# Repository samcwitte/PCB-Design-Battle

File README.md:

# PCB-Design-Battle

This is a repository containing my PCB designs for a 2-hour PCB battle I participated in with [Predictable Designs on YouTube](https://www.youtube.com/@PredictableDesigns).

The video hasn't been released yet, but I'll update this line when it is.

## Summary

This design battle was to take place over the course of 2 hours, during which the participants and I would have to complete the schematic capture and PCB layout. Here's the design guidelines we were given:

> Design a small, battery-powered PCB that reads temperature and sends the data wirelessly to a mobile app. The device must also indicate the temperature locally, this could be a display, an LED (flashing speed or color indicates temp), or something else creative. You can use any MCU, sensor, wireless method, and battery type (rechargeable, coin cells, or alkalines). You have 2 hours to complete the design.

There are two folders in this repository.
- `ESP_32_Battle` is my official end result of the 2 hour battle
- `ESP_32_Battle_4h` is the result of giving myself an additional 2 hours to work on the PCB

I took inspiration from a few of my previous ESP32 designs, of which this board shares many similarities.

While I hope they would work if made, I make no guarantees to the functionality of these PCBs.

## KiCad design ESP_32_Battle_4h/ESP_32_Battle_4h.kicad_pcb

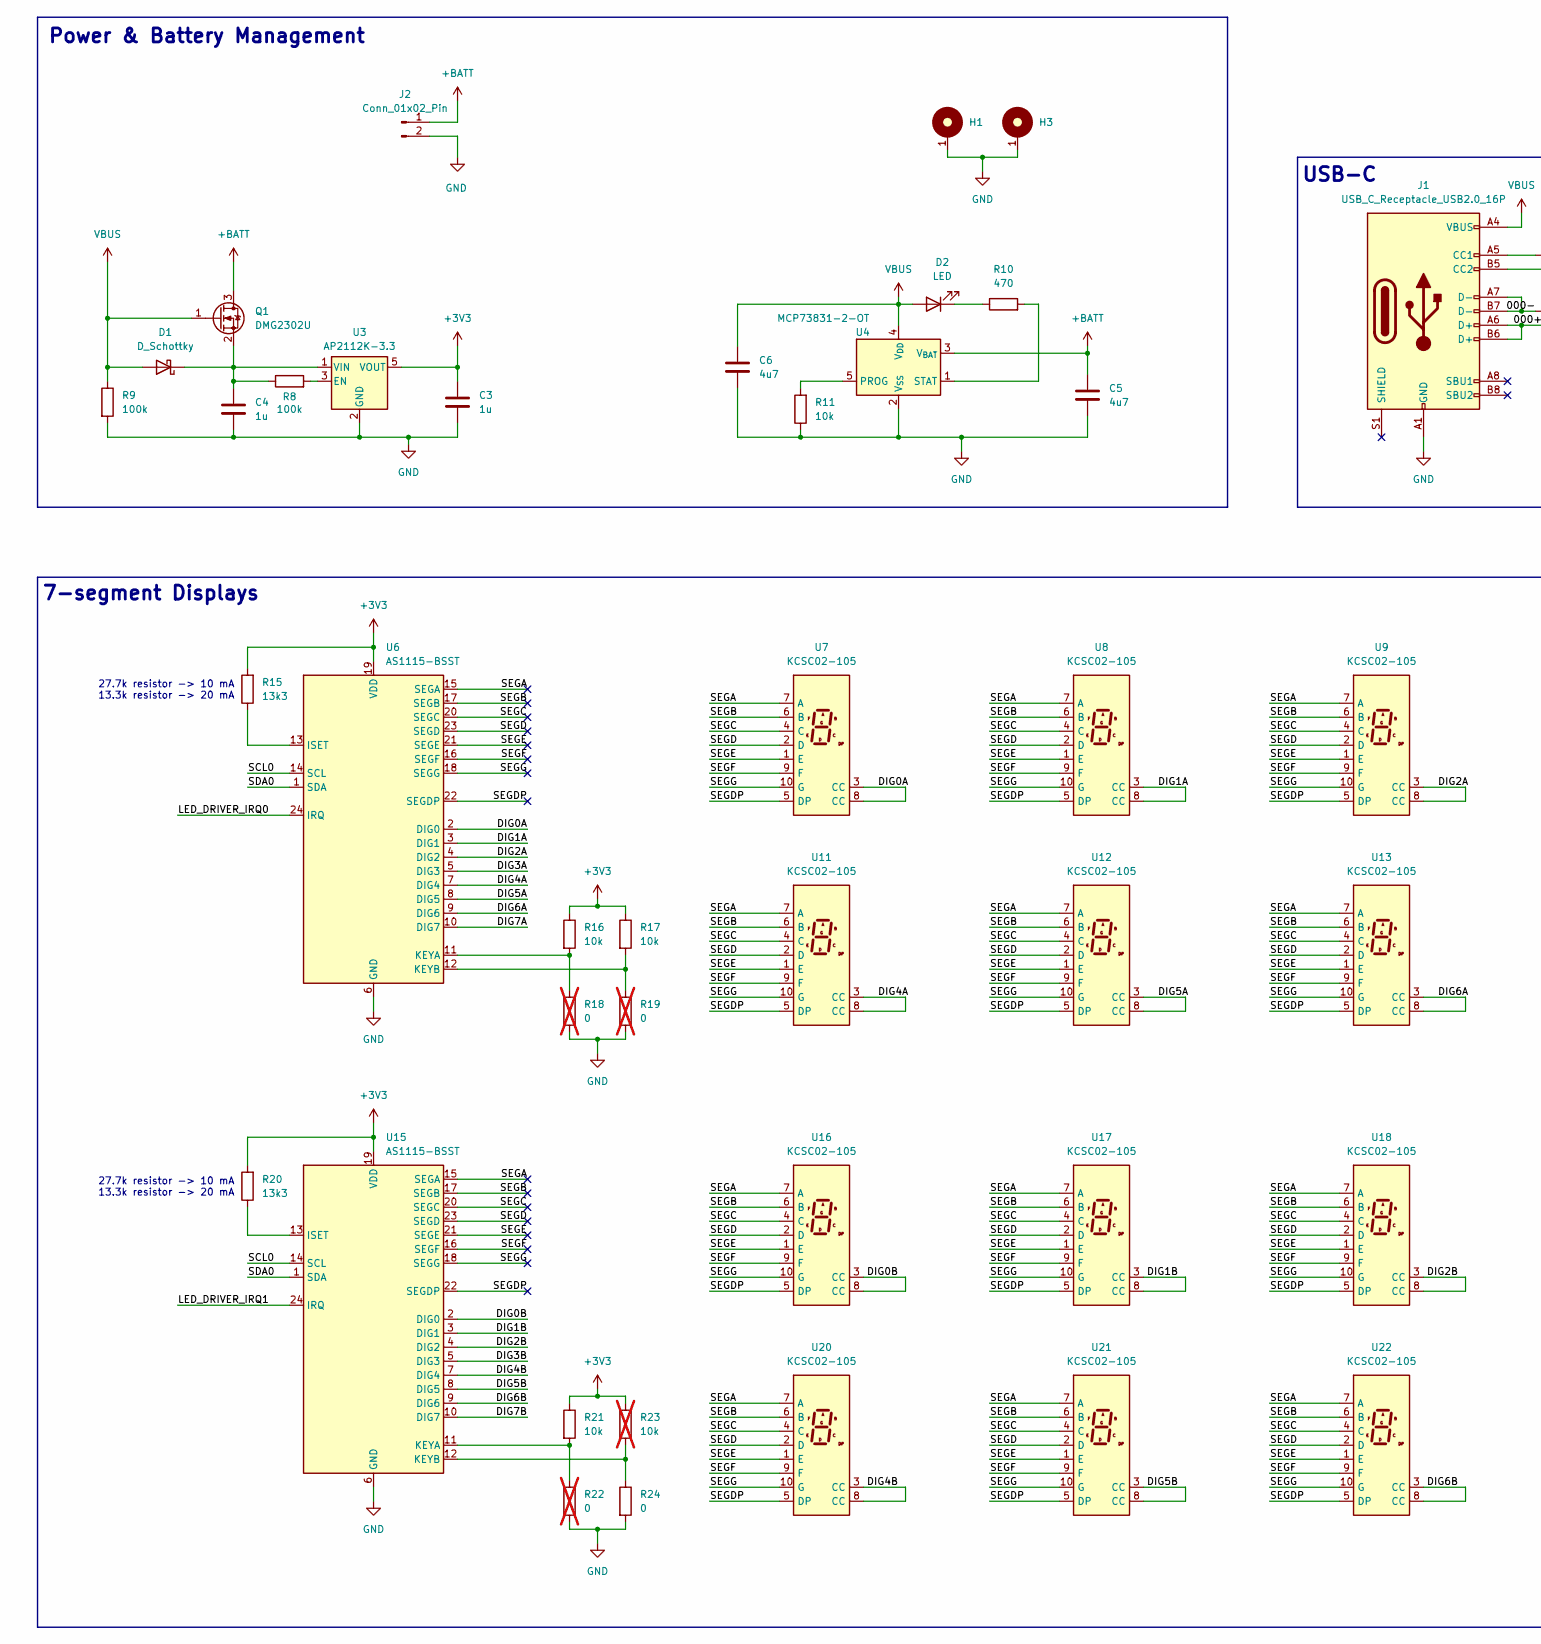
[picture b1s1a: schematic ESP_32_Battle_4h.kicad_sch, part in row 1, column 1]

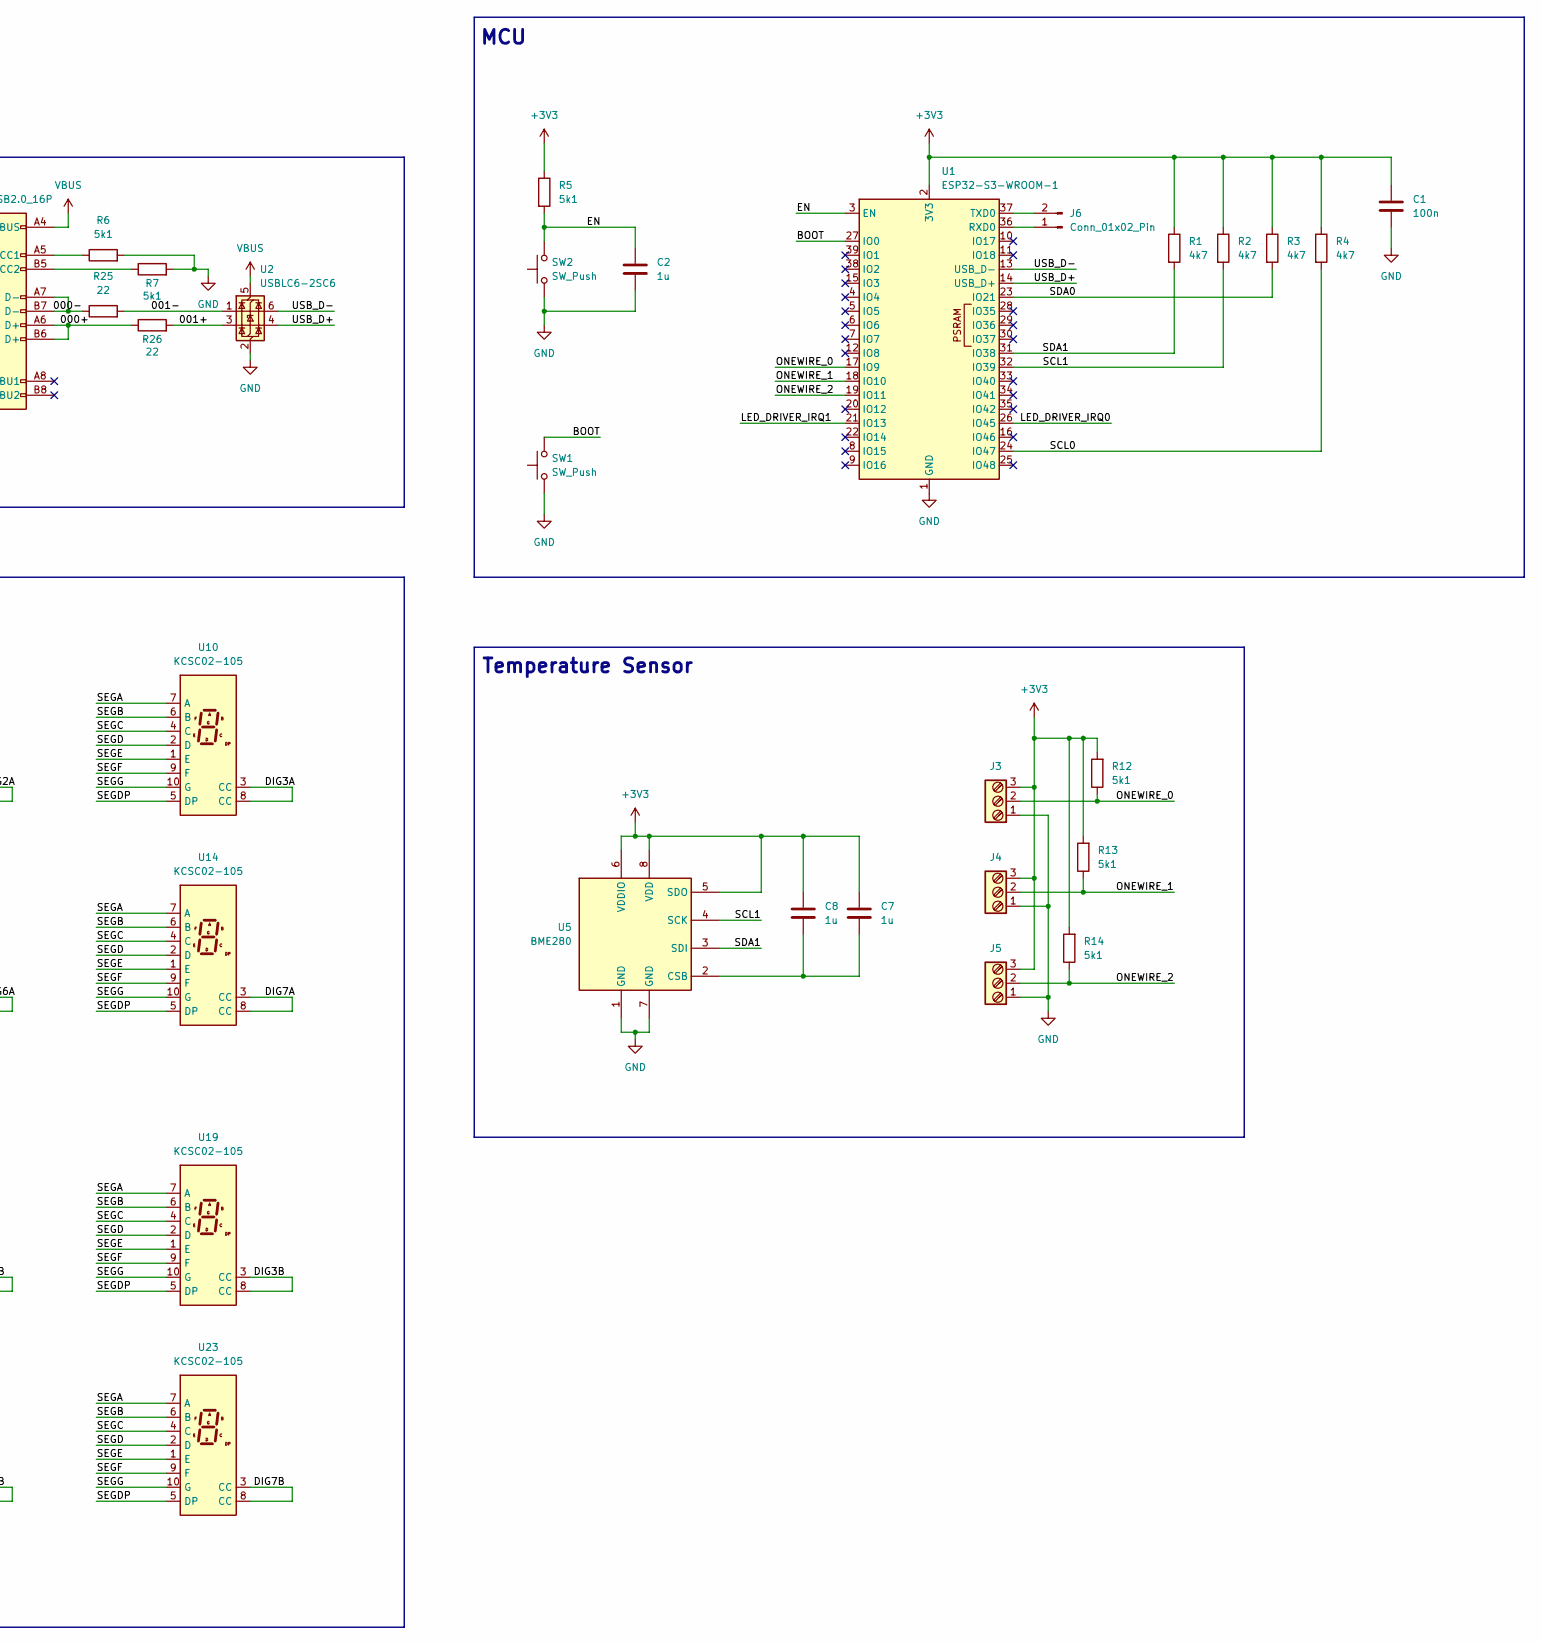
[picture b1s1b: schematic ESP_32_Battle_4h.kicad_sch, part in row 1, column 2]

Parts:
C1: 100n; C_0603_1608Metric
C2, C3, C4, C7, C8: 1u; C_0603_1608Metric
C5, C6: 4u7; C_0603_1608Metric
D1: D_Schottky; D_0603_1608Metric
D2: LED; LED_0603_1608Metric
H1, H3: MountingHole_M3_3.2mm_Pad; MountingHole_3.2mm_Pad
J1: USB_C_Receptacle_USB2.0_16P; USB_C_Receptacle_GCT_USB4105-xx-A_16P_TopMnt_Horizontal
J2: Conn_01x02_Pin; JST_PH_B2B-PH-K_1x02_P2.00mm_Vertical
J3, J4, J5: Screw_Terminal_3_P5.00mm; TerminalBlock_Phoenix_PT-1,5-3-5.0-H_1x03_P5.00mm_Horizontal
J6: Conn_01x02_Pin; PinHeader_1x02_P2.54mm_Vertical
Q1: DMG2302U; SOT-23
R1, R2, R3, R4: 4k7; R_0603_1608Metric
R5, R6, R7, R12, R13, R14: 5k1; R_0603_1608Metric
R8, R9: 100k; R_0603_1608Metric
R10: 470; R_0603_1608Metric
R11, R16, R17, R21: 10k; R_0603_1608Metric
R15, R20: 13k3; R_0603_1608Metric
R18, R19, R22: 0; R_0603_1608Metric; not fitted
R23: 10k; R_0603_1608Metric; not fitted
R24: 0; R_0603_1608Metric
R25, R26: 22; R_0603_1608Metric
SW1, SW2: SW_Push; SW_SPST_B3U-1000P
U1: ESP32-S3-WROOM-1
U2: USBLC6-2SC6; SOT-23-6
U3: AP2112K-3.3; SOT-23-5
U4: MCP73831-2-OT; SOT-23-5
U5: BME280; Bosch_LGA-8_2.5x2.5mm_P0.65mm_ClockwisePinNumbering
U6, U15: AS1115-BSST; QSOP-24_3.9x8.7mm_P0.635mm
U7, U8, U9, U10, U11, U12, U13, U14, U16, U17, U18, U19, U20, U21, U22, U23: KCSC02-105

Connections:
+3V3: C1.1, C3.1, C7.1, C8.1, J3.3, J4.3, J5.3, R1.1, R2.1, R3.1, R4.1, R5.1, R12.2, R13.2, R14.2, R15.2, R16.1, R17.1, R20.2, R21.1, R23.1, U1.2 (3V3), U3.5 (VOUT), U5.5 (SDO), U5.6 (VDDIO), U5.8 (VDD), U6.19 (VDD), U15.19 (VDD)
+BATT: C5.1, J2.1, Q1.3 (D), U4.3 (V_{BAT})
/000+: J1.A6 (D+), J1.B6 (D+), R26.1
/000-: J1.A7 (D-), J1.B7 (D-), R25.1
/001+: R26.2, U2.3 (I/O2)
/001-: R25.2, U2.1 (I/O1)
/BOOT: SW1.2, U1.27 (IO0)
/DIG0A: U6.2 (DIG0), U7.3 (CC), U7.8 (CC)
/DIG0B: U15.2 (DIG0), U16.3 (CC), U16.8 (CC)
/DIG1A: U6.3 (DIG1), U8.3 (CC), U8.8 (CC)
/DIG1B: U15.3 (DIG1), U17.3 (CC), U17.8 (CC)
/DIG2A: U6.4 (DIG2), U9.3 (CC), U9.8 (CC)
/DIG2B: U15.4 (DIG2), U18.3 (CC), U18.8 (CC)
/DIG3A: U6.5 (DIG3), U10.3 (CC), U10.8 (CC)
/DIG3B: U15.5 (DIG3), U19.3 (CC), U19.8 (CC)
/DIG4A: U6.7 (DIG4), U11.3 (CC), U11.8 (CC)
/DIG4B: U15.7 (DIG4), U20.3 (CC), U20.8 (CC)
/DIG5A: U6.8 (DIG5), U12.3 (CC), U12.8 (CC)
/DIG5B: U15.8 (DIG5), U21.3 (CC), U21.8 (CC)
/DIG6A: U6.9 (DIG6), U13.3 (CC), U13.8 (CC)
/DIG6B: U15.9 (DIG6), U22.3 (CC), U22.8 (CC)
/DIG7A: U6.10 (DIG7), U14.3 (CC), U14.8 (CC)
/DIG7B: U15.10 (DIG7), U23.3 (CC), U23.8 (CC)
/EN: C2.1, R5.2, SW2.2, U1.3 (EN)
/LED_DRIVER_IRQ0: U1.26 (IO45), U6.24 (IRQ)
/LED_DRIVER_IRQ1: U1.21 (IO13), U15.24 (IRQ)
/ONEWIRE_0: J3.2, R12.1, U1.17 (IO9)
/ONEWIRE_1: J4.2, R13.1, U1.18 (IO10)
/ONEWIRE_2: J5.2, R14.1, U1.19 (IO11)
/SCL0: R4.2, U1.24 (IO47), U6.14 (SCL), U15.14 (SCL)
/SCL1: R2.2, U1.32 (IO39), U5.4 (SCK)
/SDA0: R3.2, U1.23 (IO21), U6.1 (SDA), U15.1 (SDA)
/SDA1: R1.2, U1.31 (IO38), U5.3 (SDI)
/SEGA: U6.15 (SEGA), U7.7 (A), U8.7 (A), U9.7 (A), U10.7 (A), U11.7 (A), U12.7 (A), U13.7 (A), U14.7 (A), U15.15 (SEGA), U16.7 (A), U17.7 (A), U18.7 (A), U19.7 (A), U20.7 (A), U21.7 (A), U22.7 (A), U23.7 (A)
/SEGB: U6.17 (SEGB), U7.6 (B), U8.6 (B), U9.6 (B), U10.6 (B), U11.6 (B), U12.6 (B), U13.6 (B), U14.6 (B), U15.17 (SEGB), U16.6 (B), U17.6 (B), U18.6 (B), U19.6 (B), U20.6 (B), U21.6 (B), U22.6 (B), U23.6 (B)
/SEGC: U6.20 (SEGC), U7.4 (C), U8.4 (C), U9.4 (C), U10.4 (C), U11.4 (C), U12.4 (C), U13.4 (C), U14.4 (C), U15.20 (SEGC), U16.4 (C), U17.4 (C), U18.4 (C), U19.4 (C), U20.4 (C), U21.4 (C), U22.4 (C), U23.4 (C)
/SEGD: U6.23 (SEGD), U7.2 (D), U8.2 (D), U9.2 (D), U10.2 (D), U11.2 (D), U12.2 (D), U13.2 (D), U14.2 (D), U15.23 (SEGD), U16.2 (D), U17.2 (D), U18.2 (D), U19.2 (D), U20.2 (D), U21.2 (D), U22.2 (D), U23.2 (D)
/SEGDP: U6.22 (SEGDP), U7.5 (DP), U8.5 (DP), U9.5 (DP), U10.5 (DP), U11.5 (DP), U12.5 (DP), U13.5 (DP), U14.5 (DP), U15.22 (SEGDP), U16.5 (DP), U17.5 (DP), U18.5 (DP), U19.5 (DP), U20.5 (DP), U21.5 (DP), U22.5 (DP), U23.5 (DP)
/SEGE: U6.21 (SEGE), U7.1 (E), U8.1 (E), U9.1 (E), U10.1 (E), U11.1 (E), U12.1 (E), U13.1 (E), U14.1 (E), U15.21 (SEGE), U16.1 (E), U17.1 (E), U18.1 (E), U19.1 (E), U20.1 (E), U21.1 (E), U22.1 (E), U23.1 (E)
/SEGF: U6.16 (SEGF), U7.9 (F), U8.9 (F), U9.9 (F), U10.9 (F), U11.9 (F), U12.9 (F), U13.9 (F), U14.9 (F), U15.16 (SEGF), U16.9 (F), U17.9 (F), U18.9 (F), U19.9 (F), U20.9 (F), U21.9 (F), U22.9 (F), U23.9 (F)
/SEGG: U6.18 (SEGG), U7.10 (G), U8.10 (G), U9.10 (G), U10.10 (G), U11.10 (G), U12.10 (G), U13.10 (G), U14.10 (G), U15.18 (SEGG), U16.10 (G), U17.10 (G), U18.10 (G), U19.10 (G), U20.10 (G), U21.10 (G), U22.10 (G), U23.10 (G)
/USB_D+: U1.14 (USB_D+), U2.4 (I/O2)
/USB_D-: U1.13 (USB_D-), U2.6 (I/O1)
GND: C1.2, C2.2, C3.2, C4.1, C5.2, C6.2, H1.1, H3.1, J1.A1 (GND), J1.A12 (GND), J1.B1 (GND), J1.B12 (GND), J2.2, J3.1, J4.1, J5.1, R6.2, R7.2, R9.2, R11.1, R18.2, R19.2, R22.2, R24.2, SW1.1, SW2.1, U1.1 (GND), U1.40 (GND), U1.41 (GND), U2.2 (GND), U3.2 (GND), U4.2 (V_{SS}), U5.1 (GND), U5.7 (GND), U6.6 (GND), U15.6 (GND)
unnamed: C4.2, D1.1 (K), Q1.2 (S), R8.1, U3.1 (VIN)
unnamed: D2.1 (K), R10.1
unnamed: J1.A5 (CC1), R6.1
unnamed: J1.B5 (CC2), R7.1
unnamed: J6.1, U1.36 (RXD0)
unnamed: J6.2, U1.37 (TXD0)
unnamed: R8.2, U3.3 (EN)
unnamed: R11.2, U4.5 (PROG)
unnamed: R10.2, U4.1 (STAT)
unnamed: C7.2, C8.2, U5.2 (CSB)
unnamed: R15.1, U6.13 (ISET)
unnamed: R16.2, R18.1, U6.11 (KEYA)
unnamed: R17.2, R19.1, U6.12 (KEYB)
unnamed: R20.1, U15.13 (ISET)
unnamed: R21.2, R22.1, U15.11 (KEYA)
unnamed: R23.2, R24.1, U15.12 (KEYB)
VBUS: C6.1, D1.2 (A), D2.2 (A), J1.A4 (VBUS), J1.A9 (VBUS), J1.B4 (VBUS), J1.B9 (VBUS), Q1.1 (G), R9.1, U2.5 (VBUS), U4.4 (V_{DD})

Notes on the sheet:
MCU
Power & Battery Management
USB-C
Temperature Sensor
27.7k resistor -> 10 mA 13.3k resistor -> 20 mA
7-segment Displays

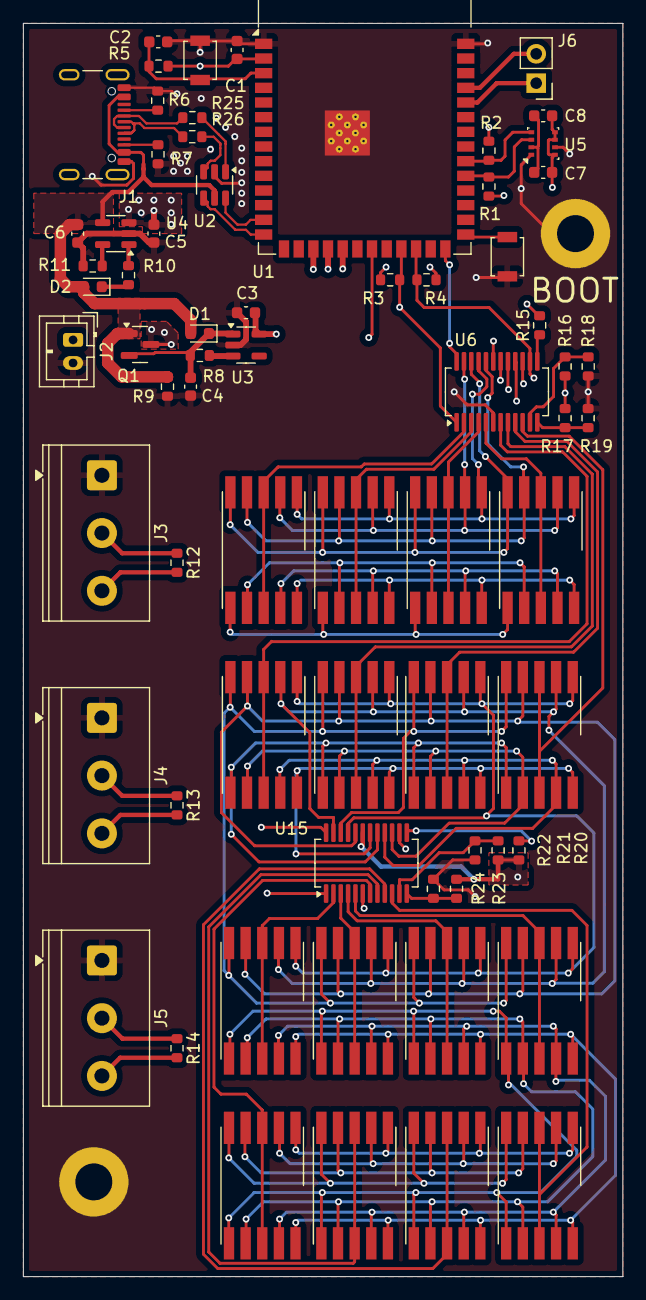
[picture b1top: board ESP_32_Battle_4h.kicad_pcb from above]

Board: 4 copper layers, 51.9 x 108.5 mm, 70 parts (0 on the bottom side), 61 nets.

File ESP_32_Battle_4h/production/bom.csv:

Designator,Footprint,Quantity,Value,LCSC Part #
C1,0603,1,100n,
"C2, C3, C4, C7, C8",0603,5,1u,
"C5, C6",0603,2,4u7,
D1,0603,1,D_Schottky,
D2,0603,1,LED,
"H1, H3",MountingHole_3.2mm_Pad,2,MountingHole_M3_3.2mm_Pad,
J1,USB_C_Receptacle_GCT_USB4105-xx-A_16P_TopMnt_Horizontal,1,USB_C_Receptacle_USB2.0_16P,
J2,JST_PH_B2B-PH-K_1x02_P2.00mm_Vertical,1,Conn_01x02_Pin,
"J3, J4, J5","TerminalBlock_Phoenix_PT-1,5-3-5.0-H_1x03_P5.00mm_Horizontal",3,Screw_Terminal_3_P5.00mm,
J6,PinHeader_1x02_P2.54mm_Vertical,1,Conn_01x02_Pin,
Q1,SOT-23,1,DMG2302U,
"R1, R2, R3, R4",0603,4,4k7,
R10,0603,1,470,
"R11, R16, R17, R21, R23",0603,5,10k,
"R12, R13, R14, R6, R7",0603,5,5k1,
"R15, R20",0603,2,13k3,
"R18, R19, R22, R24",0603,4,0,
"R25, R26",0603,2,22,
R5,0603,1,R,
"R8, R9",0603,2,100k,
"SW1, SW2",SW_SPST_B3U-1000P,2,SW_Push,
U1,ESP32-S3-WROOM-1,1,ESP32-S3-WROOM-1,
"U10, U11, U12, U13, U14, U16, U17, U18, U19, U20, U21, U22, U23, U7, U8, U9",KCSC02-105,16,KCSC02-105,
"U15, U6",QSOP-24_3.9x8.7mm_P0.635mm,2,AS1115-BSST,
U2,SOT-23-6,1,USBLC6-2SC6,
U3,SOT-23-5,1,AP2112K-3.3,
U4,SOT-23-5,1,MCP73831-2-OT,
U5,Bosch_LGA-8_2.5x2.5mm_P0.65mm_ClockwisePinNumbering,1,BME280,

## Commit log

2025-06-04 Uploaded ESP_32_Battle and ESP_32_Battle_4h KiCad project files
2025-06-04 Uploaded photos of layout and schematic
